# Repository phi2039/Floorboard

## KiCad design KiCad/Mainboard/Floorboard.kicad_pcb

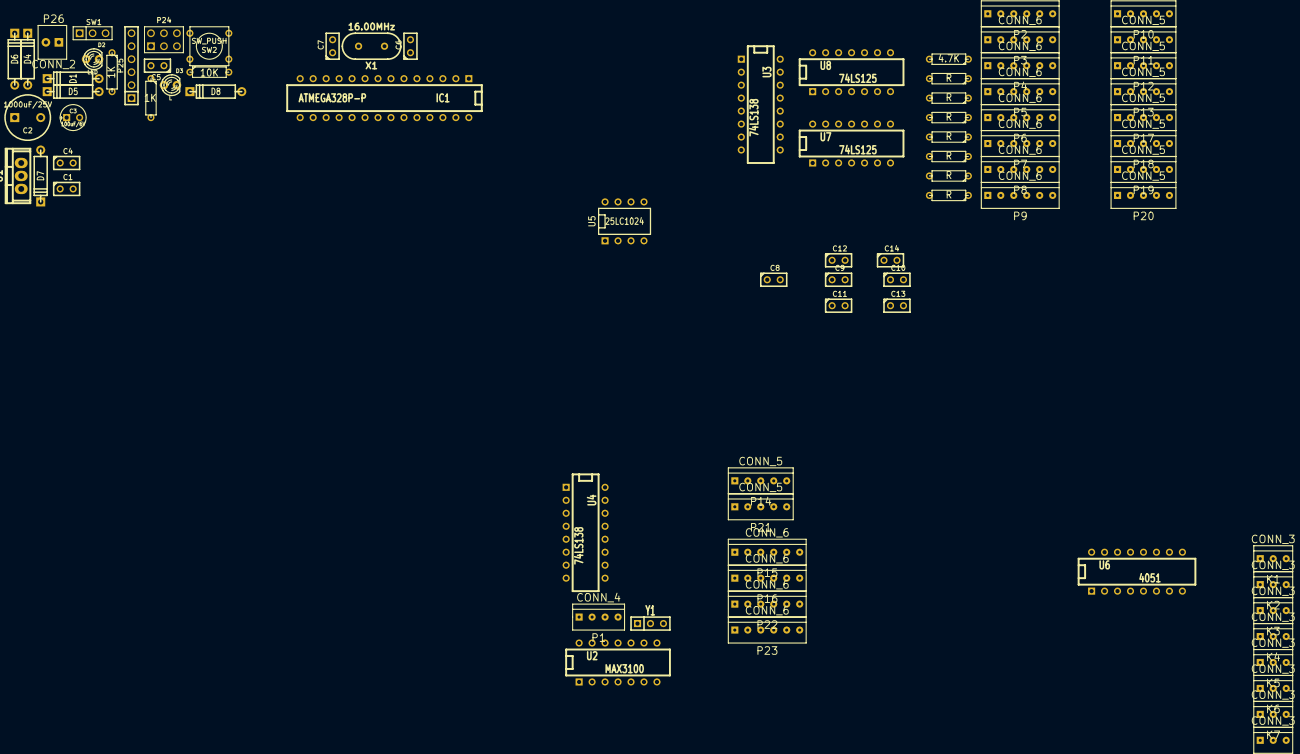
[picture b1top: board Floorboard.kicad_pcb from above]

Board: 2 copper layers, 80 parts (0 on the bottom side), 63 nets, no tracks yet.

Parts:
C1, C4, C5, C8, C9, C10, C11, C12, C13, C14: 0.1uF; C1
C2: 1000uF/25V; C2V8
C3: 100uF/6V; C1V5
C6, C7: 22pf; C1
D1, D4, D5, D6, D7: 1N4007; D4
D2: LED; LED-3MM
D3: L; LED-3MM
D8: 1N4001; D4
IC1: ATMEGA328P-P; DIP-28__300
K1, K2, K3, K4, K5, K6, K7, K8: CONN_3; TE_CONN_EI_3
P1: CONN_4; TE_CONN_EI_4
P2, P3, P4, P5, P6, P7, P8, P9, P15, P16, P22, P23: CONN_6; TE_CONN_EI_6
P10, P11, P12, P13, P14, P17, P18, P19, P20, P21: CONN_5; TE_CONN_EI_5
P24: CONN_3X2; pin_array_3x2
P25: CONN_6; PIN_ARRAY-6X1
P26: CONN_2; TE_CONN_TERM_2
R1, R11: 1K; R3
R2: 4.7K; R3
R3, R4, R5, R6, R7, R8, R9: R; R3
R10: 10K; R3
SW1: POWER_SEL; PIN_ARRAY_3X1
SW2: SW_PUSH; SW_PUSH_SMALL
U1: LM7805CT; TO-220
U2: MAX3100; DIP-14__300
U3, U4: 74LS138; DIP-16__300
U5: 25LC1024; DIP-8__300
U6: 4051; DIP-16__300
U7, U8: 74LS125; DIP-14__300
X1: 16.00MHz; HC-49V
Y1: 4MHz; SIL-3

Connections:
+5V: C8.1, C9.1, C10.1, C11.1, C12.1, C13.2, C14.2, D8.2, IC1.7, IC1.20, P1.1, P2.1, P3.1, P4.1, P5.1, P6.1, P7.1, P8.1, P9.1, P10.1, P11.1, P12.1, P13.1, P14.1, P15.1, P16.1, P17.1, P18.1, P19.1, P20.1, P21.1, P22.1, P23.1, P24.2, R10.1, U2.6, U2.14, U3.6, U3.16, U4.16, U5.3, U5.7, U5.8, U6.16, U7.14, U8.14
+9V: C1.1, C2.1, D4.2, D6.2, D7.2, U1.1
/IO/A0: IC1.4, U3.1, U4.1, U6.11
/IO/A1: IC1.5, U3.2, U4.2, U6.10
/IO/A2: IC1.6, U3.3, U4.3, U6.9
/IO/A3: IC1.11, U3.5, U4.6
/IO/ADDR_EN: IC1.15, U3.4, U4.4, U6.6
/IO/ANA0: K1.3, U6.13
/IO/ANA1: K2.3, U6.14
/IO/ANA2: K3.3, U6.15
/IO/ANA3: K4.3, U6.12
/IO/ANA4: K5.3, U6.1
/IO/ANA5: K6.3, U6.5
/IO/ANA6: K7.3, U6.2
/IO/ANA7: K8.3, U6.4
/IO/ANA_REF: IC1.21, K1.1, K2.1, K3.1, K4.1, K5.1, K6.1, K7.1, K8.1
/IO/CS0: P10.5, U3.15, U7.1
/IO/CS1: P11.5, U3.14, U7.4
/IO/CS2: P12.5, U3.13, U7.10
/IO/CS3: P13.5, U3.12, U7.13
/IO/CS4: P17.5, U3.11, U8.1
/IO/CS5: P18.5, U3.10, U8.4
/IO/CS6: P19.5, U3.9, U8.10
/IO/CS7: P20.5, U3.7, U8.13
/IO/CS8: U4.15, U5.1
/IO/CS9: P14.5, U4.14
/IO/CS10: U2.4, U4.13
/IO/CS11: P21.5, U4.12
/IO/CS12: P15.6, U4.11
/IO/CS13: P16.6, U4.10
/IO/CS14: P22.6, U4.9
/IO/CS15: P23.6, U4.7
/MCU/A0: IC1.23, U6.3
/MCU/D10: IC1.16, P2.6, P3.6, P4.6, P5.6, P6.6, P7.6, P8.6, P9.6
/MCU/D11: IC1.17, P10.3, P11.3, P12.3, P13.3, P14.3, P15.3, P16.3, P17.3, P18.3, P19.3, P20.3, P21.3, P22.3, P23.3, P24.4, U2.1, U5.5
/MCU/D12: IC1.18, P15.4, P16.4, P22.4, P23.4, P24.1, U2.2, U5.2, U7.3, U7.6, U7.8, U7.11, U8.3, U8.6, U8.8, U8.11
/MCU/D13: IC1.19, P2.5, P3.5, P4.5, P5.5, P6.5, P7.5, P8.5, P9.5, P10.4, P11.4, P12.4, P13.4, P14.4, P15.5, P16.5, P17.4, P18.4, P19.4, P20.4, P21.4, P22.5, P23.5, P24.3, R11.1, U2.3, U5.6
/MCU/RTS: C5.2, P25.6
/MCU/RX: IC1.2, P25.5
/MCU/TX: IC1.3, P25.4
/MCU/USB_5V: P25.3, SW1.3
/VIN_0: D5.2, D6.1, P26.1
/VIN_1: D1.2, D4.1, P26.2
GND: C1.2, C2.2, C3.2, C4.2, C6.1, C7.1, C8.2, C9.2, C10.2, C11.2, C12.2, C13.1, C14.1, D1.1, D3.2, D5.1, IC1.8, IC1.22, K1.2, K2.2, K3.2, K4.2, K5.2, K6.2, K7.2, K8.2, P1.2, P2.2, P2.4, P3.2, P3.4, P4.2, P4.4, P5.2, P5.4, P6.2, P6.4, P7.2, P7.4, P8.2, P8.4, P9.2, P9.4, P10.2, P11.2, P12.2, P13.2, P14.2, P15.2, P16.2, P17.2, P18.2, P19.2, P20.2, P21.2, P22.2, P23.2, P24.6, P25.1, P25.2, R1.2, R2.2, R3.2, R4.2, R5.2, R6.2, R7.2, R8.2, R9.2, SW2.2, U1.2, U2.7, U2.10, U3.8, U4.5, U4.8, U5.4, U6.7, U6.8, U7.7, U8.7, Y1.2
unnamed: C3.1, C4.1, D7.1, SW1.1, U1.3
unnamed: C5.1, D8.1, IC1.1, P24.5, R10.2, SW2.1
unnamed: C6.2, IC1.9, X1.1
unnamed: C7.2, IC1.10, X1.2
unnamed: D2.1, SW1.2
unnamed: D2.2, R1.1
unnamed: D3.1, R11.2
unnamed: P1.3, U2.13
unnamed: P1.4, U2.12
unnamed: P2.3, R2.1, U7.2
unnamed: P3.3, R3.1, U7.5
unnamed: P4.3, R4.1, U7.9
unnamed: P5.3, R5.1, U7.12
unnamed: P6.3, R6.1, U8.2
unnamed: P7.3, R7.1, U8.5
unnamed: P8.3, R8.1, U8.9
unnamed: P9.3, R9.1, U8.12
unnamed: U2.8, Y1.1
unnamed: U2.9, Y1.3

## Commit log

2014-03-26 Initial Commit
    Basic I/O Functionality
2014-03-26 Combined I/O Handling
    Put input/output shift register handling in the same place for improved
    efficiency (one loop instead of two)
2014-04-02 Redesigned I/O Structure
    Arrange modules in paired banks (0-4). Force input and output scanning
    simultaneously
2014-04-02 Hardware SPI / 8 Banks
    Switch from SW to HW SPI and add additional input bus driver
2014-04-02 Code Cleanup
2014-04-02 Latching input tests...
2014-04-02 EEPROM Handling
2014-04-09 Lots of changes...
2014-04-11 Added external UART (MAX3100)
2014-04-28 Schematics and board design
2014-04-28 Initial Board Layout
